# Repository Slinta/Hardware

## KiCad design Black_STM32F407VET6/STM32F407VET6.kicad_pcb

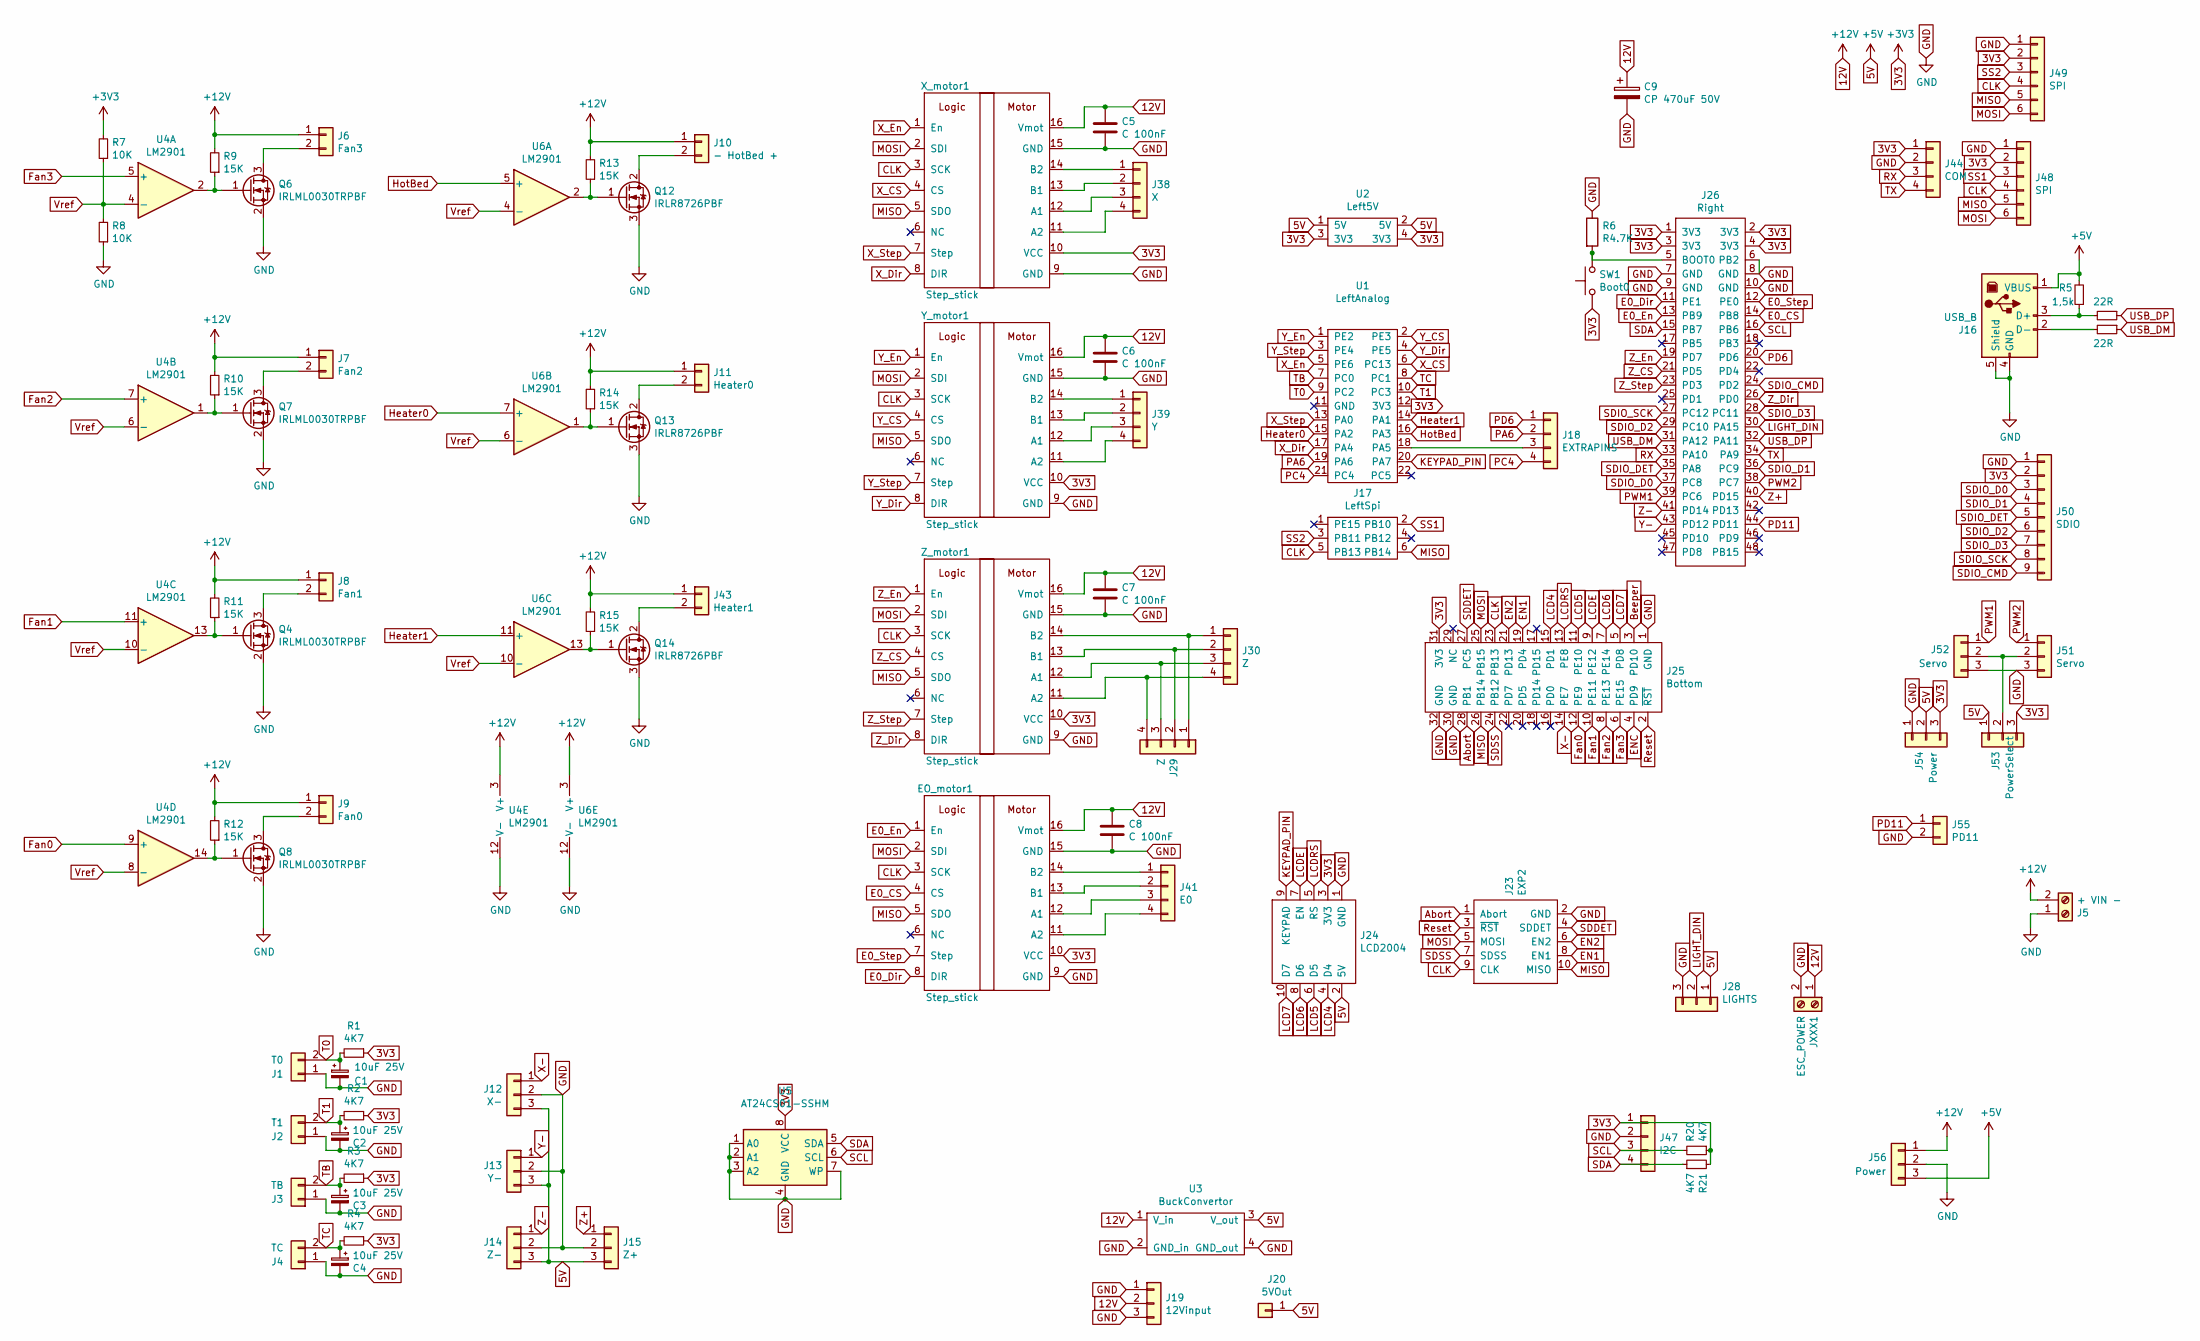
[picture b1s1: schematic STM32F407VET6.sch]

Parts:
C1, C2, C3, C4: 10uF 25V; CP_Radial_D4.0mm_P2.00mm
C5, C6, C7, C8: C 100nF; C_Disc_D3.4mm_W2.1mm_P2.50mm
C9: CP 470uF 50V; CP_Radial_D10.0mm_P5.00mm
EO_motor1: Step_stick; Motor
J1: T0; JST_XH_B2B-XH-AM_1x02_P2.50mm_Vertical
J2: T1; JST_XH_B2B-XH-AM_1x02_P2.50mm_Vertical
J3: TB; JST_XH_B2B-XH-AM_1x02_P2.50mm_Vertical
J4: TC; JST_XH_B2B-XH-AM_1x02_P2.50mm_Vertical
J5: + VIN -; KF7.62_2P
J6: Fan3; JST_XH_B2B-XH-AM_1x02_P2.50mm_Vertical
J7: Fan2; JST_XH_B2B-XH-AM_1x02_P2.50mm_Vertical
J8: Fan1; JST_XH_B2B-XH-AM_1x02_P2.50mm_Vertical
J9: Fan0; JST_XH_B2B-XH-AM_1x02_P2.50mm_Vertical
J10: - HotBed +; KF7.62_2P
J11: Heater0; TerminalBlock_bornier-2_P5.08mm
J12: X-; JST_XH_B3B-XH-A_1x03_P2.50mm_Vertical
J13: Y-; JST_XH_B3B-XH-A_1x03_P2.50mm_Vertical
J14: Z-; JST_XH_B3B-XH-A_1x03_P2.50mm_Vertical
J15: Z+; JST_XH_B3B-XH-A_1x03_P2.50mm_Vertical
J16: USB_B; USB_B_OST_USB-B1HSxx_Horizontal
J17: LeftSpi; PinHeader_2x03_P2.54mm_Vertical
J18: EXTRAPINS; PinHeader_1x04_P2.54mm_Vertical
J19: 12Vinput; PinHeader_1x03_P2.54mm_Vertical
J20: 5VOut; PinHeader_1x01_P2.54mm_Vertical
J23: EXP2; IDC-Header_2x05_P2.54mm_Vertical
J24: LCD2004; IDC-Header_2x05_P2.54mm_Vertical
J25: Bottom; PinSocket_2x16_P2.54mm_Vertical
J26: Right; PinSocket_2x24_P2.54mm_Vertical
J28: LIGHTS; JST_XH_B3B-XH-A_1x03_P2.50mm_Vertical
J29, J30: Z; JST_XH_B4B-XH-A_1x04_P2.50mm_Vertical
J38: X; JST_XH_B4B-XH-A_1x04_P2.50mm_Vertical
J39: Y; JST_XH_B4B-XH-A_1x04_P2.50mm_Vertical
J41: E0; JST_XH_B4B-XH-A_1x04_P2.50mm_Vertical
J43: Heater1; TerminalBlock_bornier-2_P5.08mm
J44: COM; PinHeader_1x04_P2.54mm_Vertical
J47: I2C; PinHeader_1x04_P2.54mm_Vertical
J48, J49: SPI; PinHeader_1x06_P2.54mm_Vertical
J50: SDIO; JST_XH_B9B-XH-A_1x09_P2.50mm_Vertical
J51, J52: Servo; PinHeader_1x03_P2.54mm_Vertical
J53: PowerSelect; PinHeader_1x03_P2.54mm_Vertical
J54, J56: Power; PinHeader_1x03_P2.54mm_Vertical
J55: PD11; PinHeader_1x02_P2.54mm_Vertical
JXXX1: ESC_POWER; TerminalBlock_bornier-2_P5.08mm
Q4, Q6, Q7, Q8: IRLML0030TRPBF; SOT-23
Q12, Q13, Q14: IRLR8726PBF; TO-252-2
R1, R2, R3, R4, R20, R21: 4K7; R_0603_1608Metric
R5: 1,5k; R_0603_1608Metric
R6: R4.7K; R_0603_1608Metric
R7, R8: 10K; R_0603_1608Metric
R9, R10, R11, R12, R13, R14, R15: 15K; R_0603_1608Metric
R18, R19: 22R; R_0603_1608Metric
SW1: Boot0; SW_PUSH_6mm_H5mm
U1: LeftAnalog; PinHeader_2x11_P2.54mm_Vertical
U2: Left5V; PinHeader_2x02_P2.54mm_Vertical
U3: BuckConvertor; MP2307Buck
U4, U6: LM2901; SOIC-14_3.9x8.7mm_P1.27mm
U5: AT24CS01-SSHM; SOIC-8_3.9x4.9mm_P1.27mm
X_motor1: Step_stick; Motor
Y_motor1: Step_stick; Motor
Z_motor1: Step_stick; Motor

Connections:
3V3: EO_motor1.10 (VCC), J24.3 (3V3), J25.31 (3V3), J26.1 (3V3), J26.2 (3V3), J26.3 (3V3), J26.4 (3V3), J44.1, J47.1, J48.2, J49.2, J50.2, J53.3, J54.3, R1.1, R2.1, R3.1, R4.1, R7.2, R20.1, R21.2, SW1.1, U1.12 (3V3), U2.3 (3V3), U2.4 (3V3), U5.8 (VCC), X_motor1.10 (VCC), Y_motor1.10 (VCC), Z_motor1.10 (VCC)
5V: J12.3, J13.3, J14.3, J15.3, J16.1 (VBUS), J20.1, J24.2 (5V), J28.1, J53.1, J54.2, J56.3, R5.2, U2.1 (5V), U2.2 (5V), U3.3 (V_out)
12V: C5.1, C6.1, C7.1, C8.1, C9.1, EO_motor1.16 (Vmot), J5.2, J6.1, J7.1, J8.1, J9.1, J10.1, J11.1, J19.2, J43.1, J56.1, JXXX1.1, R9.2, R10.2, R11.2, R12.2, R13.2, R14.2, R15.2, U3.1 (V_in), U4.3 (V+), U6.3 (V+), X_motor1.16 (Vmot), Y_motor1.16 (Vmot), Z_motor1.16 (Vmot)
Abort: J23.1 (Abort), J25.28 (PB1)
Beeper: J25.3 (PD10)
CLK: EO_motor1.3 (SCK), J17.5 (PB13), J23.9 (CLK), J25.23 (PB13), J48.4, J49.4, X_motor1.3 (SCK), Y_motor1.3 (SCK), Z_motor1.3 (SCK)
E0_CS: EO_motor1.4 (CS), J26.14 (PB8)
E0_Dir: EO_motor1.8 (DIR), J26.11 (PE1)
E0_En: EO_motor1.1 (En), J26.13 (PB9)
E0_Step: EO_motor1.7 (Step), J26.12 (PE0)
EN1: J23.8 (EN1), J25.19 (PD4)
EN2: J23.6 (EN2), J25.21 (PD13)
ENC: J25.4 (PD9)
GND: C1.2, C2.2, C3.2, C4.2, C5.2, C6.2, C7.2, C8.2, C9.2, EO_motor1.9 (GND), EO_motor1.15 (GND), J1.1, J2.1, J3.1, J4.1, J5.1, J12.2, J13.2, J14.2, J15.2, J16.4 (GND), J16.5 (Shield), J19.1, J19.3, J23.2 (GND), J24.1 (GND), J25.1 (GND), J25.30 (GND), J25.32 (GND), J26.6 (PB2), J26.7 (GND), J26.8 (GND), J26.9 (GND), J26.10 (GND), J28.3, J44.2, J47.2, J48.1, J49.1, J50.1, J51.3, J52.3, J54.1, J55.2, J56.2, JXXX1.2, Q4.2 (S), Q6.2 (S), Q7.2 (S), Q8.2 (S), Q12.3 (S), Q13.3 (S), Q14.3 (S), R6.1, R8.1, U3.2 (GND_in), U3.4 (GND_out), U4.12 (V-), U5.1 (A0), U5.2 (A1), U5.3 (A2), U5.4 (GND), U5.7 (WP), U6.12 (V-), X_motor1.9 (GND), X_motor1.15 (GND), Y_motor1.9 (GND), Y_motor1.15 (GND), Z_motor1.9 (GND), Z_motor1.15 (GND)
Heater0: U1.15 (PA2), U6.7 (+)
Heater1: U1.14 (PA1), U6.11 (+)
HotBed: U1.16 (PA3), U6.5 (+)
KEYPAD_PIN: J24.9 (KEYPAD), U1.20 (PA7)
LCD4: J24.4 (D4), J25.15 (PD1)
LCD5: J24.6 (D5), J25.11 (PE10)
LCD6: J24.8 (D6), J25.7 (PE14)
LCD7: J24.10 (D7), J25.5 (PD8)
LCDE: J24.7 (EN), J25.9 (PE12)
LCDRS: J24.5 (RS), J25.13 (PE8)
LIGHT_DIN: J26.30 (PA15), J28.2
MISO: EO_motor1.5 (SDO), J17.6 (PB14), J23.10 (MISO), J25.26 (PB14), J48.5, J49.5, X_motor1.5 (SDO), Y_motor1.5 (SDO), Z_motor1.5 (SDO)
MOSI: EO_motor1.2 (SDI), J23.5 (MOSI), J25.25 (PB15), J48.6, J49.6, X_motor1.2 (SDI), Y_motor1.2 (SDI), Z_motor1.2 (SDI)
unnamed: EO_motor1.11 (A2), J41.4
unnamed: EO_motor1.12 (A1), J41.3
unnamed: EO_motor1.13 (B1), J41.2
unnamed: EO_motor1.14 (B2), J41.1
unnamed: J6.2, Q6.3 (D)
unnamed: J7.2, Q7.3 (D)
unnamed: J8.2, Q4.3 (D)
unnamed: J9.2, Q8.3 (D)
unnamed: J10.2, Q12.2 (D)
unnamed: J11.2, Q13.2 (D)
unnamed: J16.2 (D-), R18.2
unnamed: J16.3 (D+), R5.1, R19.2
unnamed: J18.3, U1.18 (PA5)
unnamed: J26.5 (BOOT0), R6.2, SW1.2
unnamed: J29.1, J30.1, Z_motor1.14 (B2)
unnamed: J29.2, J30.2, Z_motor1.13 (B1)
unnamed: J29.3, J30.3, Z_motor1.12 (A1)
unnamed: J29.4, J30.4, Z_motor1.11 (A2)
unnamed: J38.1, X_motor1.14 (B2)
unnamed: J38.2, X_motor1.13 (B1)
unnamed: J38.3, X_motor1.12 (A1)
unnamed: J38.4, X_motor1.11 (A2)
unnamed: J39.1, Y_motor1.14 (B2)
unnamed: J39.2, Y_motor1.13 (B1)
unnamed: J39.3, Y_motor1.12 (A1)
unnamed: J39.4, Y_motor1.11 (A2)
unnamed: J43.2, Q14.2 (D)
unnamed: J51.2, J52.2, J53.2
unnamed: Q4.1 (G), R11.1, U4.13
unnamed: Q6.1 (G), R9.1, U4.2
unnamed: Q7.1 (G), R10.1, U4.1
unnamed: Q8.1 (G), R12.1, U4.14
unnamed: Q12.1 (G), R13.1, U6.2
unnamed: Q13.1 (G), R14.1, U6.1
unnamed: Q14.1 (G), R15.1, U6.13
PA6: J18.2, U1.19 (PA6)
PC4: J18.4, U1.21 (PC4)
PD6: J18.1, J26.20 (PD6)
PD11: J26.44 (PD11), J55.1
PWM1: J26.39 (PC6), J52.1
PWM2: J26.38 (PC7), J51.1
RX: J26.33 (PA10), J44.3
Reset: J23.3 (~RST), J25.2 (~RST)
SCL: J26.16 (PB6), J47.3, R20.2, U5.6 (SCL)
SDA: J26.15 (PB7), J47.4, R21.1, U5.5 (SDA)
SDDET: J23.4 (SDDET), J25.27 (PC5)
SDIO_CMD: J26.24 (PD2), J50.9
SDIO_D0: J26.37 (PC8), J50.3
SDIO_D1: J26.36 (PC9), J50.4
SDIO_D2: J26.29 (PC10), J50.6
SDIO_D3: J26.28 (PC11), J50.7
SDIO_DET: J26.35 (PA8), J50.5
SDIO_SCK: J26.27 (PC12), J50.8
SDSS: J23.7 (SDSS), J25.24 (PB12)
SS1: J17.2 (PB10), J48.3
SS2: J17.3 (PB11), J49.3
T0: C1.1, J1.2, R1.2, U1.9 (PC2)
T1: C2.1, J2.2, R2.2, U1.10 (PC3)
TB: C3.1, J3.2, R3.2, U1.7 (PC0)
TC: C4.1, J4.2, R4.2, U1.8 (PC1)
TX: J26.34 (PA9), J44.4
USB_DM: J26.31 (PA12), R18.1
USB_DP: J26.32 (PA11), R19.1
Vref: R7.1, R8.2, U4.4 (-), U4.6 (-), U4.8 (-), U4.10 (-), U6.4 (-), U6.6 (-), U6.10 (-)
X-: J12.1, J25.14 (PE7)
X_CS: U1.6 (PC13), X_motor1.4 (CS)
X_Dir: U1.17 (PA4), X_motor1.8 (DIR)
X_En: U1.5 (PE6), X_motor1.1 (En)
X_Step: U1.13 (PA0), X_motor1.7 (Step)
Y-: J13.1, J26.43 (PD12)
Y_CS: U1.2 (PE3), Y_motor1.4 (CS)
Y_Dir: U1.4 (PE5), Y_motor1.8 (DIR)
Y_En: U1.1 (PE2), Y_motor1.1 (En)
Y_Step: U1.3 (PE4), Y_motor1.7 (Step)
Z+: J15.1, J26.40 (PD15)
Z-: J14.1, J26.41 (PD14)
Z_CS: J26.21 (PD5), Z_motor1.4 (CS)
Z_Dir: J26.26 (PD0), Z_motor1.8 (DIR)
Z_En: J26.19 (PD7), Z_motor1.1 (En)
Z_Step: J26.23 (PD3), Z_motor1.7 (Step)

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
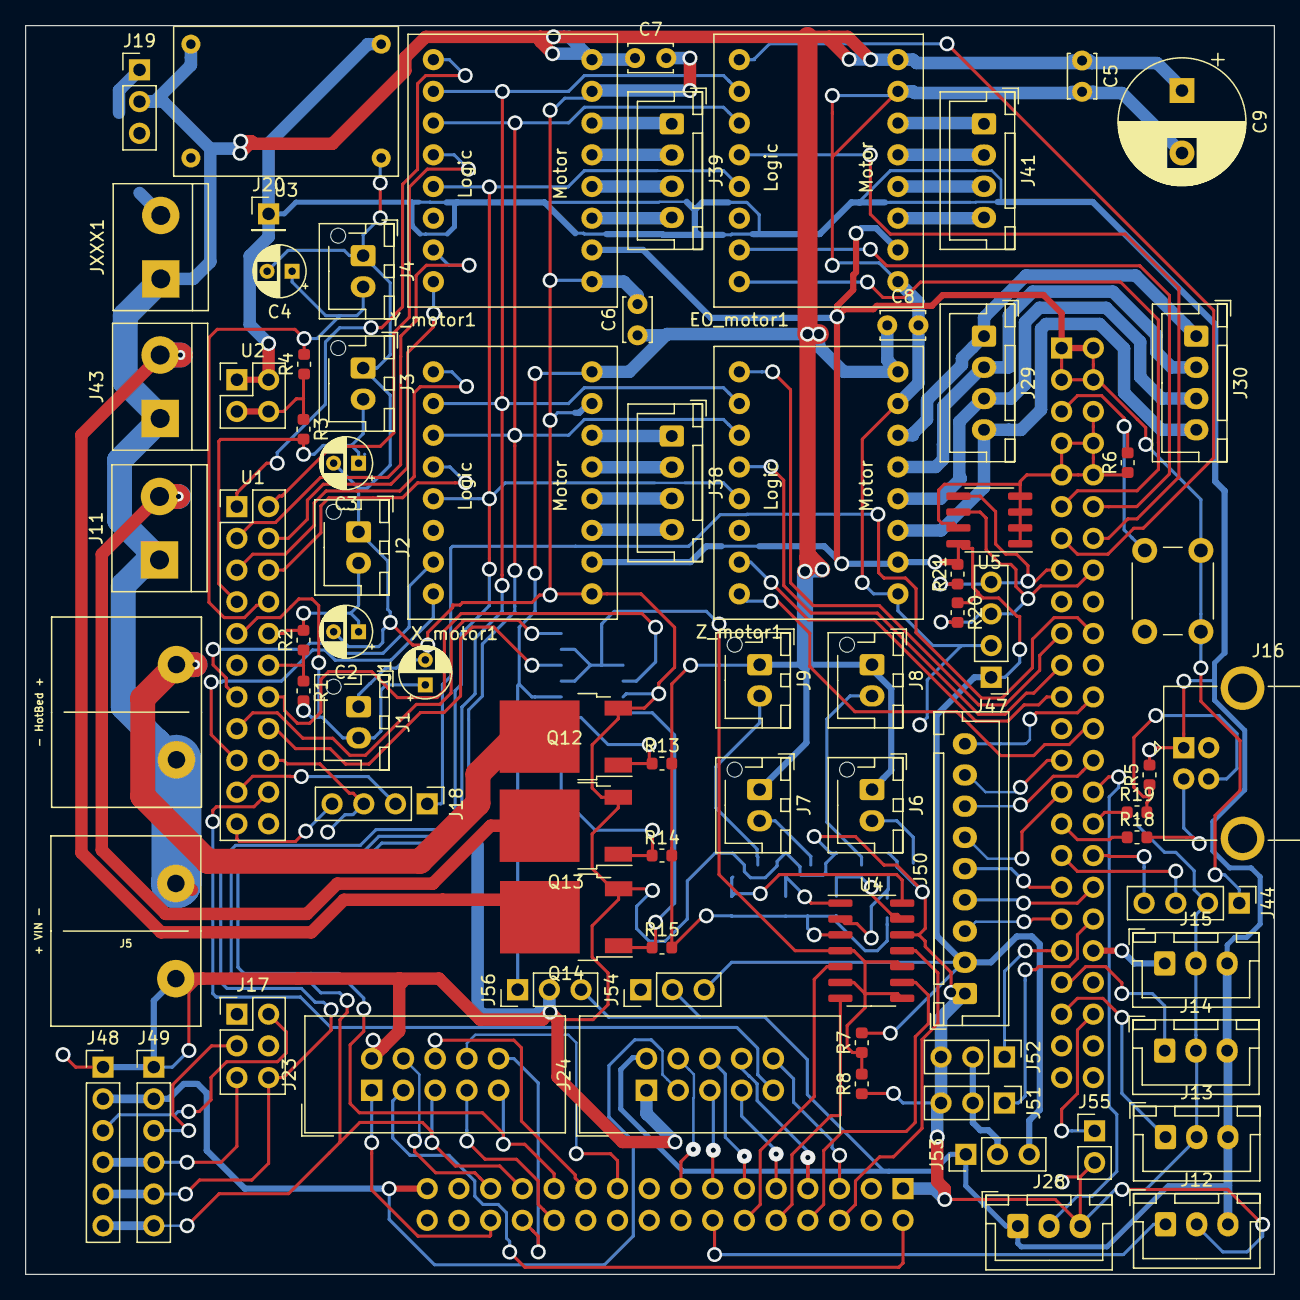
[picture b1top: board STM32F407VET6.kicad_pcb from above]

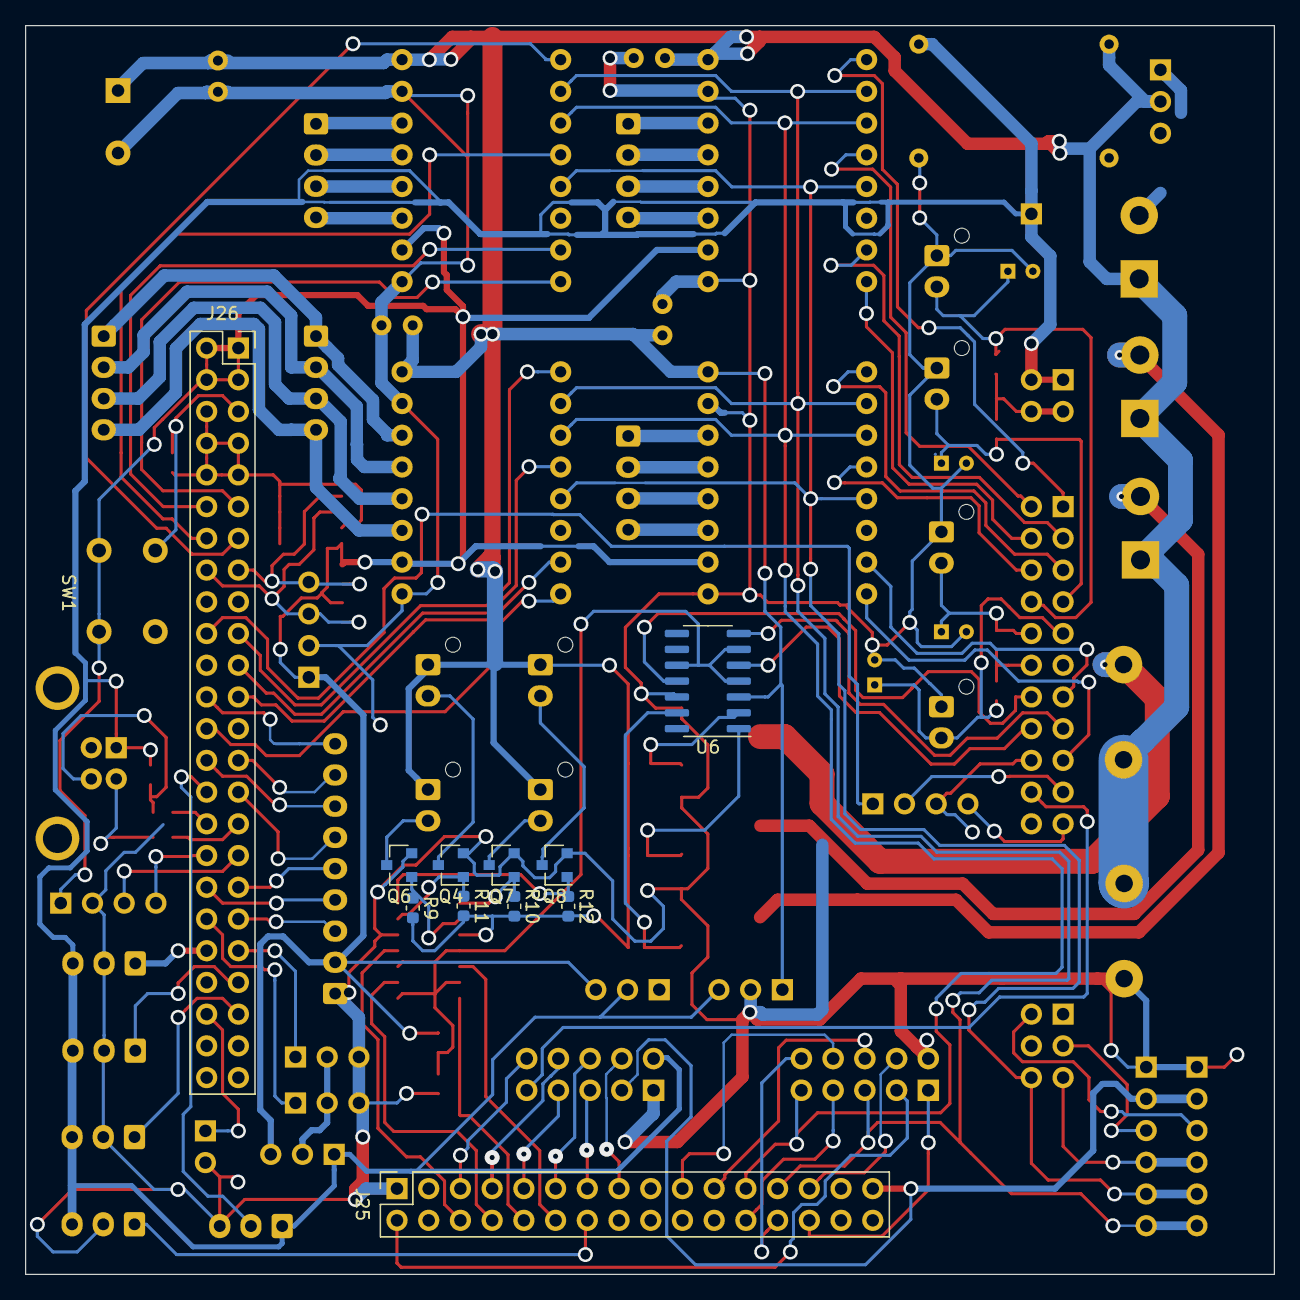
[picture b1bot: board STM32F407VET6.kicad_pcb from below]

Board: 2 copper layers, 100.0 x 100.0 mm, 89 parts (11 on the bottom side), 109 nets.

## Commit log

2019-07-08 Schematic only: TMC spi, ESC pins etc.
2019-07-09 Changed parts in schematic to be cheaper, PCB changed to be DIY friendly
2019-07-09 Arranged parts on PCB, swapped a few pins in schematic to align connectors.
2019-07-12 Flash button, Endstops, Drivers moved
2019-07-13 Rework of the PCB, made footprint for the motor drivers.
2019-07-13 Power connectors - Removed left side holes to make room for Heater and Bed traces - Moved spi connectors, temperature connectors, fan connectors - Assigned correct footprints to power connectors (KF7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
2019-07-14 Left side - Temperature sensors - Capacitor package change - Reworked left side symbols
2019-07-15 Layout finialized - finished fan section - fixed & finished temperature section - drivers positioned roughly
2019-07-17 Changed spi channel, updated design rules TODO: change all tracks to be at least 0.25 wide and fix tracks not being in the center between headers
2019-07-18 Wider tracks, more clearance, X & Y logic. SPI 1 is no longer used on shield because is used on the mcu board with different pins Added a design rule, distance between tracks is now at least 0.2925 W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
2019-07-18 Z and E0 wiring - 12V rails - TODO: spi lines
2019-07-18 Power lines
2019-07-19 Power mosfets - everything done apart from connecting GND - Are the 12V rail caps necessary ?
2019-07-24 Flipped back resistors to the front
2019-07-27 Backup update ?
2019-07-31 Added comparators to drive the mosfets.
2019-08-03 Board layout with the opamps
2019-08-07 Added fill zones
2019-08-13 Fan 12V rail separated with option for buck disabled board outline for manufacturing - moved to fab layer
2019-08-13 //Forgot to save Fan separated power rail to allow different voltage Moved border to fabrication layer to prepare for milling
